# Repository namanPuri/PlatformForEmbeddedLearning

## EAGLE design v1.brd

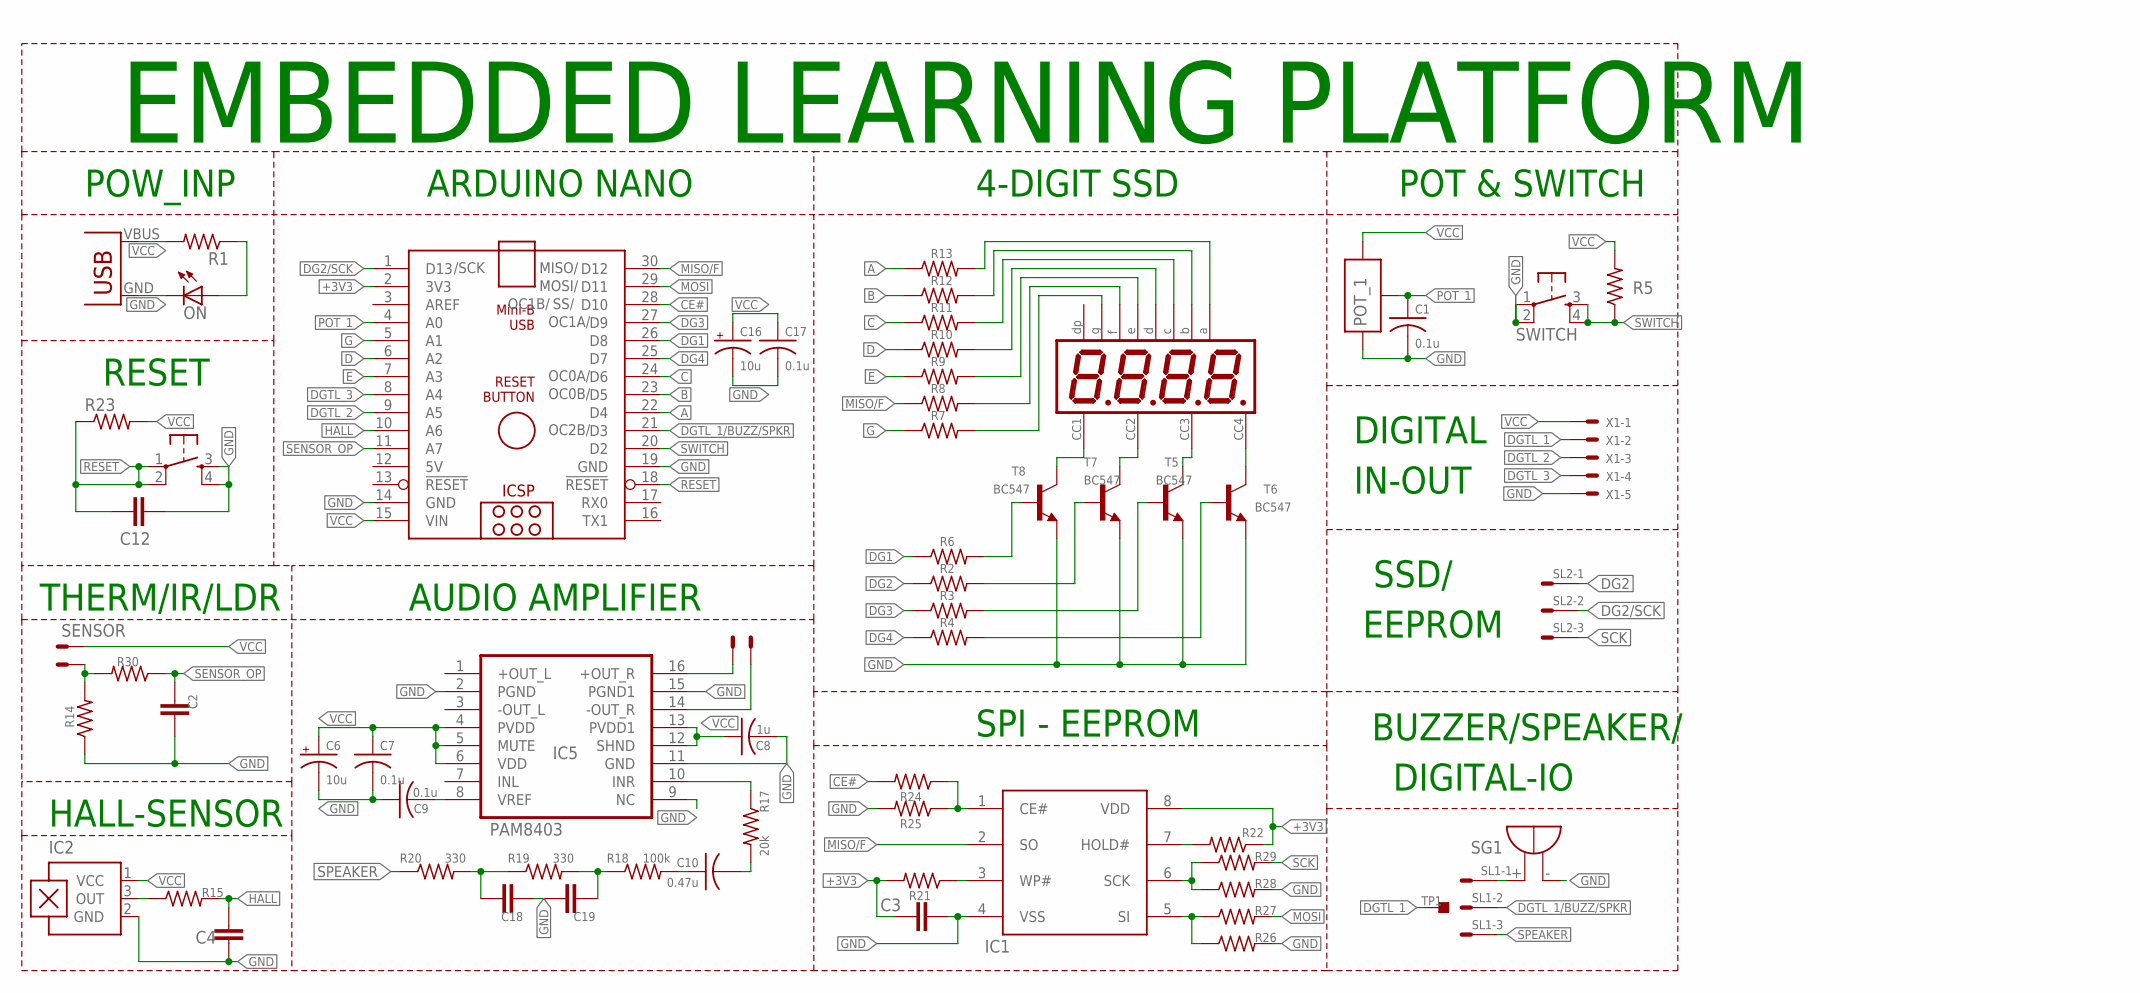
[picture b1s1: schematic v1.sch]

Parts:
ARDUINO_NANO1: ARDUINO_NANO
C1, C7, C9, C17: 0.1u; C0603
C2, C3, C4, C12, C18: 0.1u; C0805
C6, C16: 10u; B/3528-21R
C8: 1u; C0603
C10: 0.47u; C0603
C19: 0.1uf; C0805
DIS1: NFD-5641AS-ALT; NFD-5641
IC1: SST25VF040B_SPI_FLASH; SOIC08
IC2: HALL SENSOR; SIP3-UA
IC5: PAM8403; SOP-16
ON: LED3MM
POT_1: POTNORMAL; RJ9W
R1, R2, R3, R4, R5, R6, R7, R8, R9, R10, R11, R12, R13, R14, R15, R21, R22, R23, R24, R25, R26, R27, R28, R29, R30: R-US_0204/7; 0204/7
R17: 20k; M0805
R18: 100k; M0805
R19, R20: 330; M0805
RESET: 10xx; B3F-10XX
SG1: BUZZER; F/TMB
SL1, SL2: M03S; 03P
SPEAKER: SPEAKER; JST-XH-02-PACKAGE-LONG-PAD
SWITCH: OMRON_SWITCH_40-XX; B3F-40XX
T5, T6, T7, T8: BC547; TO92
TP1: TESTPOINT_TPS-PAD-036; TESTPOINT_PAD-036
U$2: USB(POWER)
X1: JST-XH-05-PIN-LONG-PAD; JST-XH-05-PACKAGE-LONG-PAD
X2: SENSOR; JST-XH-02-PACKAGE-LONG-PAD

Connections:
5V: ARDUINO_NANO1.12 (5V)
+3V3: ARDUINO_NANO1.2 (3V3), C3.1, IC1.8 (VDD), R21.2, R22.1
A: ARDUINO_NANO1.22 (D4), R13.1
B: ARDUINO_NANO1.23 (D5), R12.1
BUZZER: SG1.+, SL1.1
C: ARDUINO_NANO1.24 (D6), R11.1
CE#: ARDUINO_NANO1.28 (D10), R24.2
D: ARDUINO_NANO1.6 (A2), R10.1
DG1: ARDUINO_NANO1.26 (D8), R6.1
DG2: R2.1, SL2.1
DG2/SCK: ARDUINO_NANO1.1 (D13), SL2.2
DG3: ARDUINO_NANO1.27 (D9), R3.1
DG4: ARDUINO_NANO1.25 (D7), R4.1
DGTL_1: TP1.1, X1.2
DGTL_1/BUZZ/SPKR: ARDUINO_NANO1.21 (D3), SL1.2
DGTL_2: ARDUINO_NANO1.9 (A5), X1.3
DGTL_3: ARDUINO_NANO1.8 (A4), X1.4
E: ARDUINO_NANO1.7 (A3), R9.1
G: ARDUINO_NANO1.5 (A1), R7.1
GND: ARDUINO_NANO1.14 (GND), ARDUINO_NANO1.19 (GND), C1.2, C2.1, C3.2, C4.1, C6.-, C7.2, C8.2, C9.1, C12.2, C16.-, C17.2, C18.2, C19.2, IC1.4 (VSS), IC2.2 (GND), IC5.2 (PGND), IC5.9 (NC), IC5.11 (GND), IC5.15 (PGND1), ON.K (C), POT_1.E, R14.1, R25.2, R26.2, R28.2, RESET.3 (S), RESET.4 (S1), SG1.-, SWITCH.1, SWITCH.2 (P1), T5.1 (E), T6.1 (E), T7.1 (E), T8.1 (E), U$2.GND, X1.5
HALL: ARDUINO_NANO1.10 (A6), C4.2, R15.2
MICIN1: C19.1, R18.1, R19.2
MISO/F: ARDUINO_NANO1.30 (D12), IC1.2 (SO), R8.1
MOSI: ARDUINO_NANO1.29 (D11), R27.2
unnamed: ON.A, R1.1
unnamed: DIS1.P$12, T8.3 (C)
unnamed: DIS1.P$6, T6.3 (C)
unnamed: DIS1.P$8, T5.3 (C)
unnamed: DIS1.P$9, T7.3 (C)
unnamed: R6.2, T8.2 (B)
unnamed: R2.2, T7.2 (B)
unnamed: R3.2, T5.2 (B)
unnamed: R4.2, T6.2 (B)
unnamed: IC2.3 (OUT), R15.1
unnamed: DIS1.P$5, R7.2
unnamed: DIS1.P$10, R8.2
unnamed: DIS1.P$1, R9.2
unnamed: DIS1.P$2, R10.2
unnamed: DIS1.P$4, R11.2
unnamed: DIS1.P$7, R12.2
unnamed: DIS1.P$11, R13.2
unnamed: IC5.16 (+OUT_R), SPEAKER.1
unnamed: IC5.14 (-OUT_R), SPEAKER.2
unnamed: C9.2, IC5.8 (VREF)
unnamed: C10.2, R17.2
unnamed: IC1.7 (HOLD#), R22.2
unnamed: IC1.3 (WP#), R21.1
unnamed: IC1.1 (CE#), R24.1, R25.1
unnamed: IC1.5 (SI), R26.1, R27.1
unnamed: IC1.6 (SCK), R28.1, R29.1
unnamed: IC5.10 (INR), R17.1
unnamed: C18.1, R19.1, R20.2
unnamed: C10.1, R18.2
POT_1: ARDUINO_NANO1.4 (A0), C1.1, POT_1.S
RESET: ARDUINO_NANO1.18 (!RESET), C12.1, R23.1, RESET.1, RESET.2 (P1)
SCK: R29.2, SL2.3
SENSOR_OP: ARDUINO_NANO1.11 (A7), C2.2, R14.2, R30.1, R30.2, X2.1
SPEAKER: R20.1, SL1.3
SWITCH: ARDUINO_NANO1.20 (D2), R5.1, SWITCH.3 (S), SWITCH.4 (S1)
VCC: ARDUINO_NANO1.15 (VIN), C6.+, C7.1, C8.1, C16.+, C17.1, IC2.1 (VCC), IC5.4 (PVDD), IC5.5 (MUTE), IC5.6 (VDD), IC5.12 (SHND), IC5.13 (PVDD1), POT_1.A, R1.2, R5.2, R23.2, U$2.VBUS (VCC), X1.1, X2.2

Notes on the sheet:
/SCK
MISO/
MOSI/
SS/
OC2B/
OC0A/
OC0B/
OC1A/
OC1B/
AUDIO AMPLIFIER
POW_INP
ARDUINO NANO
4-DIGIT SSD
SPI - EEPROM
RESET
THERM/IR/LDR
BUZZER/SPEAKER/ DIGITAL-IO
POT & SWITCH
DIGITAL IN-OUT
SSD/ EEPROM
EMBEDDED LEARNING PLATFORM
HALL-SENSOR

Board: 2 copper layers, 64 parts (0 on the bottom side), 59 nets, no tracks yet.

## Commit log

2021-05-31 v1 updated
